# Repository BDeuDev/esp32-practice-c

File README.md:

# ESP32 Learning Journey

This repository documents my hands-on journey into Embedded Systems and Firmware Engineering using the ESP32 and ESP-IDF with The C Programming Language.

The goal is to learn by building. Each project focuses on a specific concept, peripheral, or embedded programming technique while improving my understanding of electronics, real-time systems, hardware debugging, and firmware development.

Rather than creating production-ready applications, this repository serves as a collection of experiments, exercises, and practical projects that help me develop embedded engineering skills.

## What I'm Learning

* GPIO and Digital Electronics
* FreeRTOS
* Timers and Scheduling
* Interrupts
* UART, SPI, and I2C
* PWM, ADC, and DAC
* Sensors and Actuators
* Wi-Fi and Bluetooth
* Hardware Debugging
* PCB Design with KiCad
* ESP-IDF Development

## Repository Structure

```mermaid
graph TD
    ROOT[ESP32 Learning Journey]

    ROOT --> BLINK[01_blink]
    ROOT --> TRAFFIC[02_traffic_light]
    ROOT --> BUTTON[03_button]
    ROOT --> PWM[04_pwm_led]
    ROOT --> ADC[05_adc_potentiometer]

    BLINK --> BLINK_README[README.md]
    BLINK --> BLINK_FW[firmware]
    BLINK --> BLINK_HW[hardware]

    TRAFFIC --> TRAFFIC_README[README.md]
    TRAFFIC --> TRAFFIC_FW[firmware]
    TRAFFIC --> TRAFFIC_HW[hardware]

    BUTTON --> BUTTON_README[README.md]
    BUTTON --> BUTTON_FW[firmware]
    BUTTON --> BUTTON_HW[hardware]

    PWM --> PWM_README[README.md]
    PWM --> PWM_FW[firmware]
    PWM --> PWM_HW[hardware]

    ADC --> ADC_README[README.md]
    ADC --> ADC_FW[firmware]
    ADC --> ADC_HW[hardware]
```

## Projects

| Project                                                   | Concept                                         |
| --------------------------------------------------------- | ----------------------------------------------- |
| [01 - Blink](./01_blink/README.md)                        | Basic GPIO output and ESP-IDF project structure |
| [02 - Traffic Light](./02_traffic_light/README.md)        | Multiple GPIO outputs and timing control        |
| [03 - Button](./03_button/README.md)                      | GPIO input, ISR and IRAM attr                   |
| [04 - PWM LED](./04_pwm_led/README.md)                    | PWM (Pulse Width Modulation)                    |
| [05 - ADC Potentiometer](./05_adc_potentiometer/README.md)| ADC (Analog-to-Digital Conversion)              |

## Why This Repository Exists

I created this repository to:

* Track my progress in embedded development.
* Document what I learn while working with ESP32 devices.
* Practice firmware engineering concepts through real projects.
* Build a portfolio that reflects my growth as an embedded developer.
* Create a reference for future projects.

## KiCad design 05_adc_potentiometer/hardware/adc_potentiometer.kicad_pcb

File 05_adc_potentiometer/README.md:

# 05 - ADC Potentiometer

A simple ESP32 project used to learn ADC (Analog-to-Digital Conversion) and how to work with a 7x4 segment display.

## Demo

## PCB Design

### Schematic

### PCB Top Layer

### PCB Bottom Layer

## 3D Model

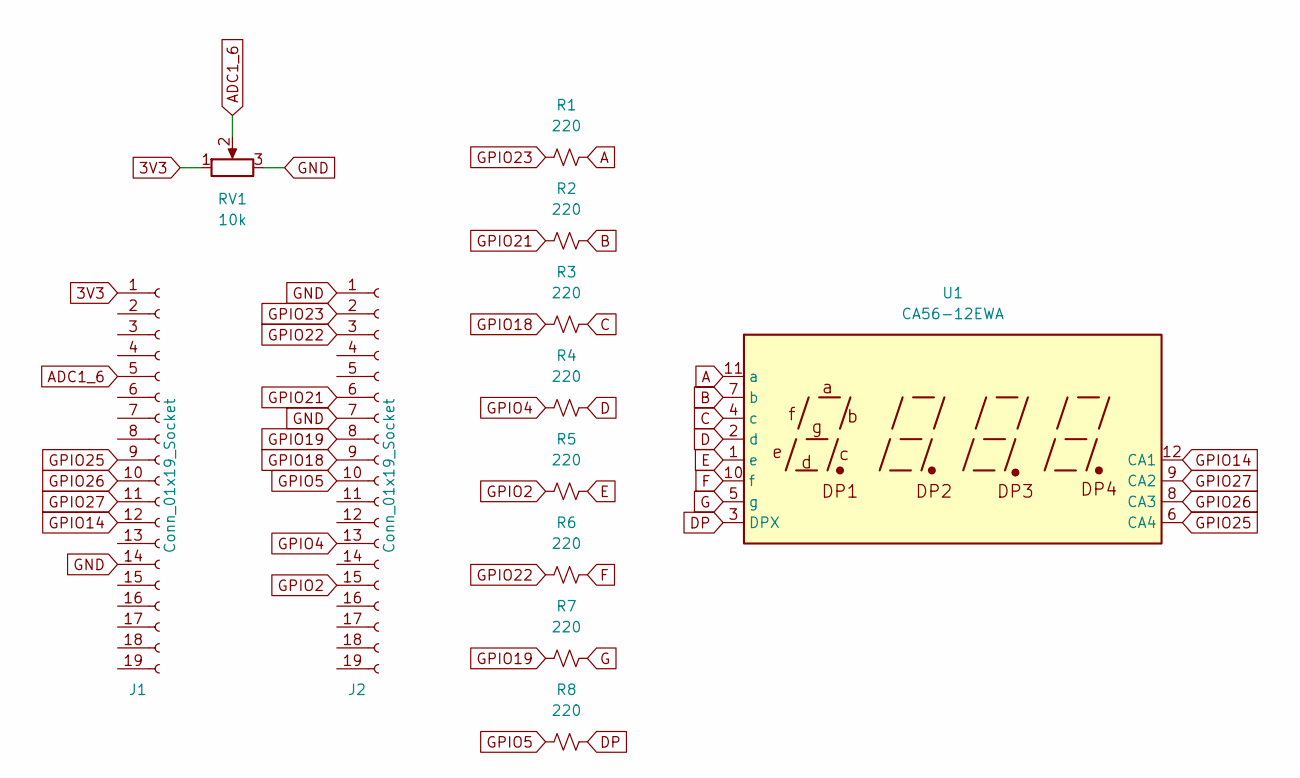
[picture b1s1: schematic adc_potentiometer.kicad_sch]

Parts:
J1, J2: Conn_01x19_Socket; PinSocket_1x19_P2.54mm_Vertical
R1, R2, R3, R4, R5, R6, R7, R8: 220; R_Axial_DIN0207_L6.3mm_D2.5mm_P15.24mm_Horizontal
RV1: 10k; Potentiometer_Bourns_3314G_Vertical
U1: CA56-12EWA; CA56-12SEKWA

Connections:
3V3: J1.1, RV1.1
A: R1.2, U1.11 (a)
ADC1_6: J1.5, RV1.2
B: R2.2, U1.7 (b)
C: R3.2, U1.4 (c)
D: R4.2, U1.2 (d)
DP: R8.2, U1.3 (DPX)
E: R5.2, U1.1 (e)
F: R6.2, U1.10 (f)
G: R7.2, U1.5 (g)
GND: J1.14, J2.1, J2.7, RV1.3
GPIO2: J2.15, R5.1
GPIO4: J2.13, R4.1
GPIO5: J2.10, R8.1
GPIO14: J1.12, U1.12 (CA1)
GPIO18: J2.9, R3.1
GPIO19: J2.8, R7.1
GPIO21: J2.6, R2.1
GPIO22: J2.3, R6.1
GPIO23: J2.2, R1.1
GPIO25: J1.9, U1.6 (CA4)
GPIO26: J1.10, U1.8 (CA3)
GPIO27: J1.11, U1.9 (CA2)

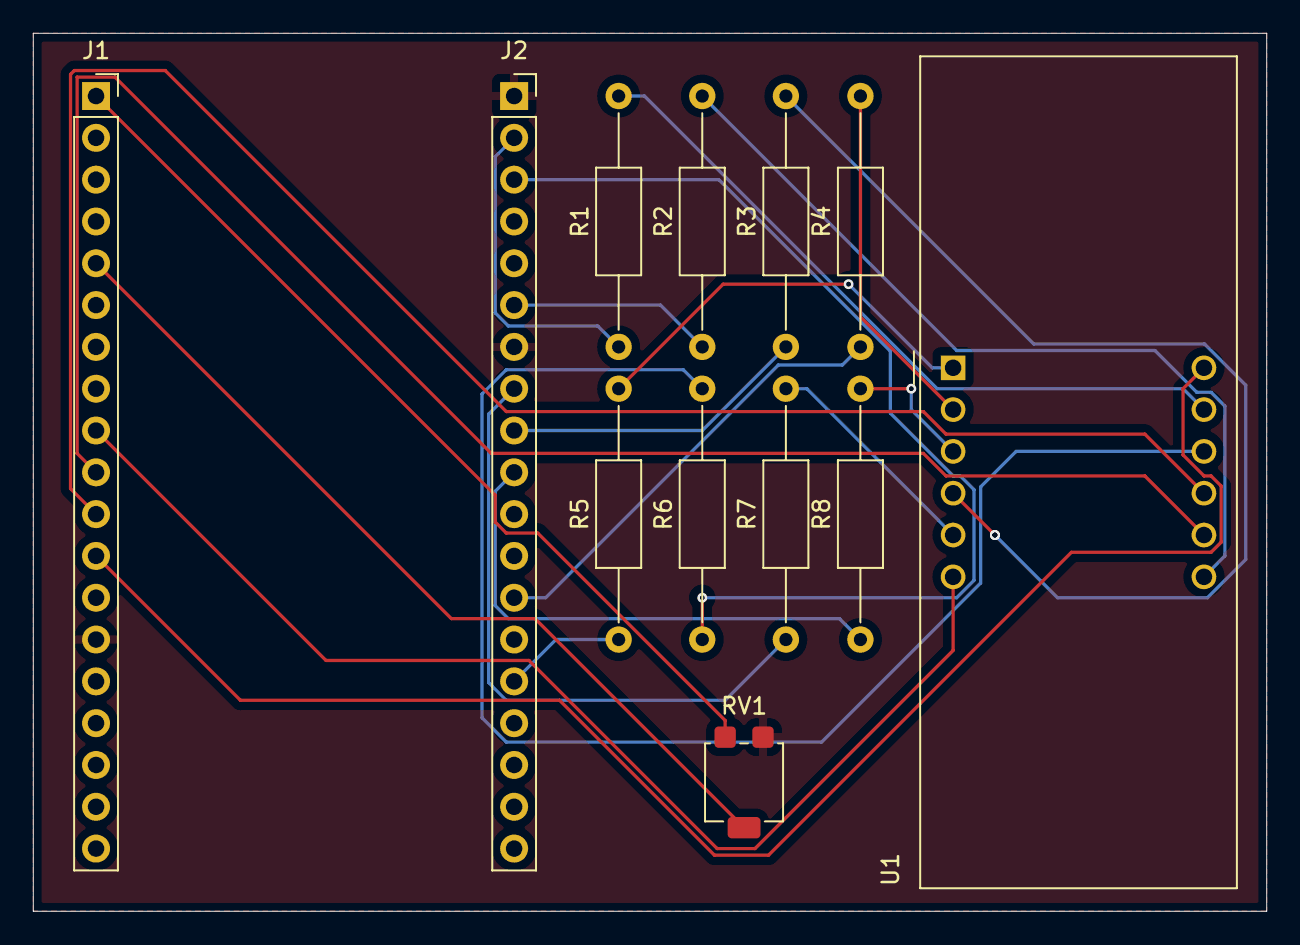
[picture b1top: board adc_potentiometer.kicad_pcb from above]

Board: 2 copper layers, 74.9 x 53.3 mm, 12 parts (0 on the bottom side), 23 nets.

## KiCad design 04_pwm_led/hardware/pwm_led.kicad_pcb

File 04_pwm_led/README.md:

# 04 - PWM LED

A simple ESP32 project used to learn PWM (Pulse Width Modulation) with duty cycles.

## Demo

## PCB Design

### Schematic

### PCB Top Layer

### PCB Bottom Layer

## 3D Model

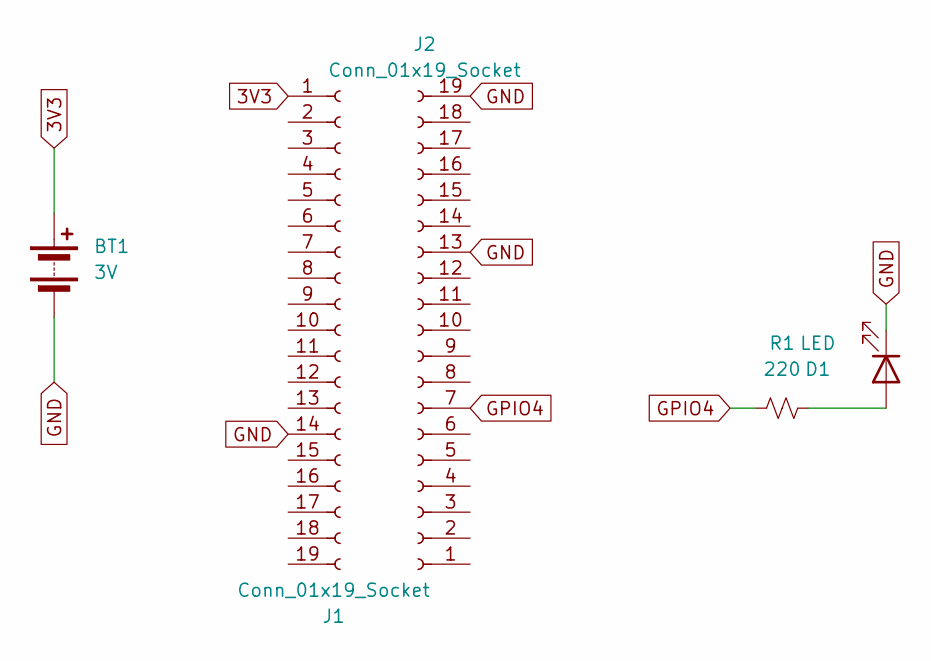
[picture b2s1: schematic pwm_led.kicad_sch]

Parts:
BT1: 3V; BatteryHolder_Keystone_2462_2xAA
D1: LED; LED_D3.0mm
J1, J2: Conn_01x19_Socket; PinSocket_1x19_P2.54mm_Vertical
R1: 220; R_Axial_DIN0204_L3.6mm_D1.6mm_P7.62mm_Horizontal

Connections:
3V3: BT1.1 (+), J1.1
GND: BT1.2 (-), D1.1 (K), J1.14, J2.13, J2.19
GPIO4: J2.7, R1.1
unnamed: D1.2 (A), R1.2

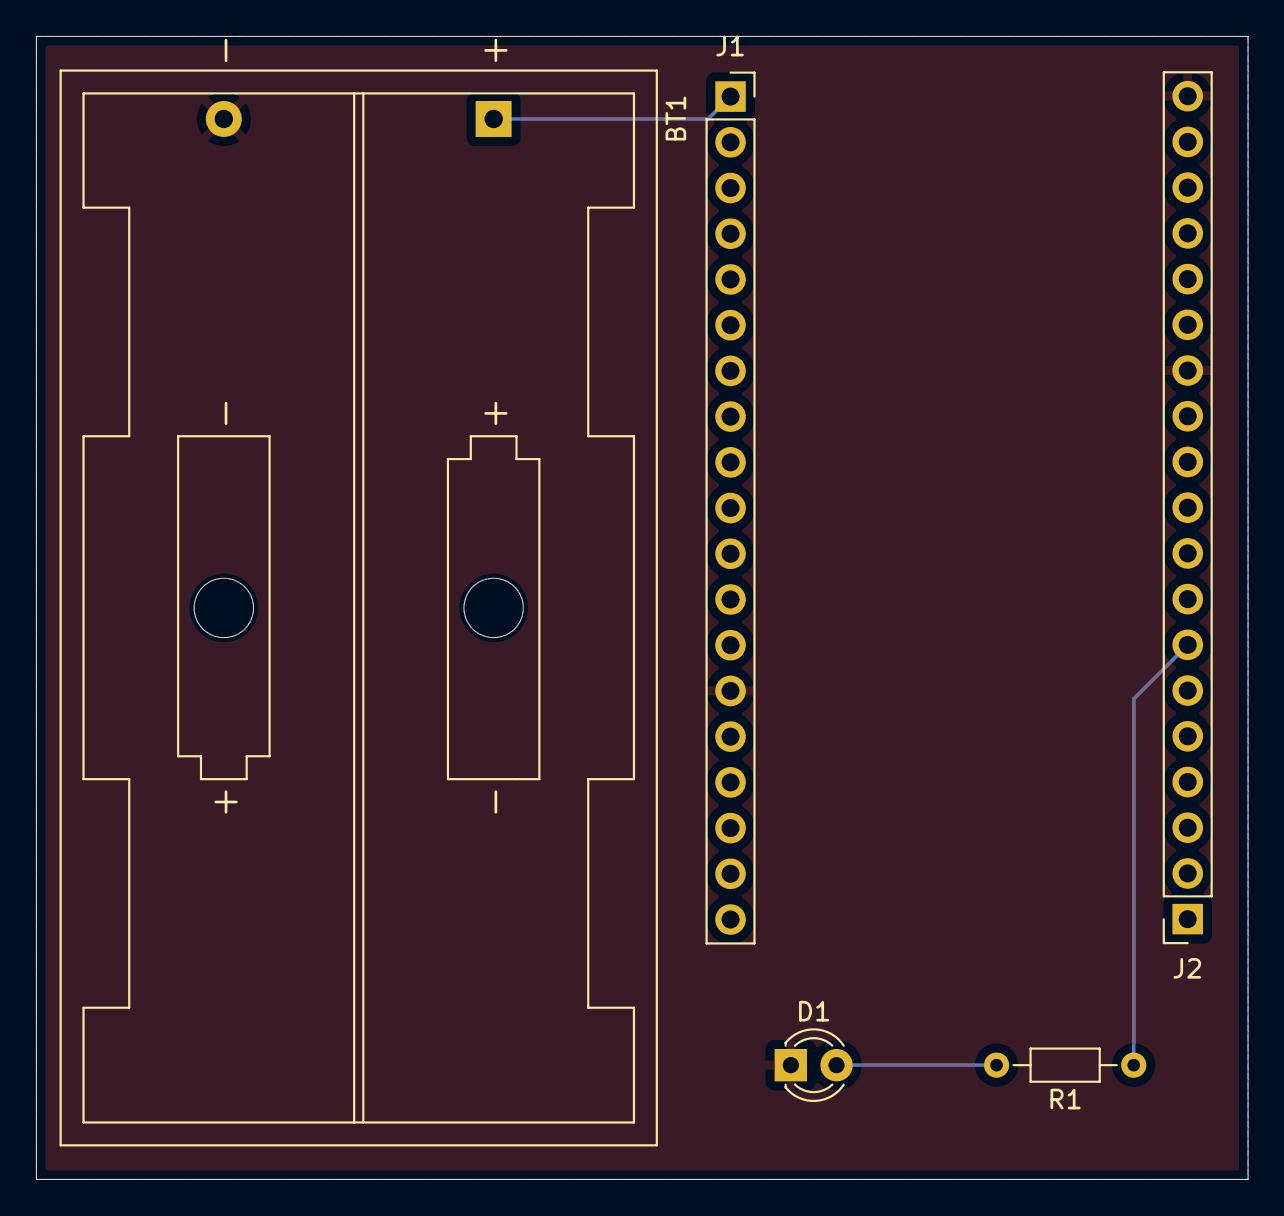
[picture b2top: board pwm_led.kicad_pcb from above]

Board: 2 copper layers, 67.3 x 63.5 mm, 5 parts (0 on the bottom side), 4 nets.

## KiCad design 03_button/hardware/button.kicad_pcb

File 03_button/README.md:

# 03 - Button

A simple ESP32 project used to learn GPIO input, events, ISR, queue, IRAM attr.

## Demo

## PCB Design

### Schematic

### PCB Top Layer

### PCB Bottom Layer

## 3D Model

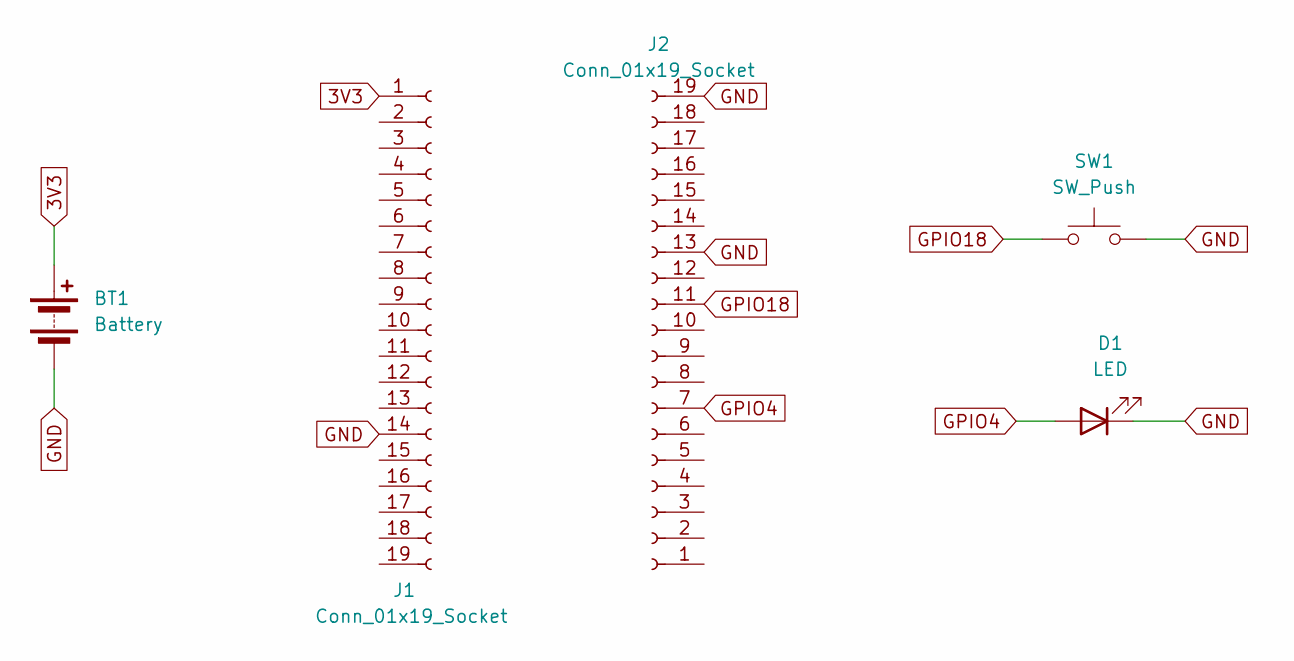
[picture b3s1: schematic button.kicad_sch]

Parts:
BT1: Battery; BatteryHolder_Keystone_2462_2xAA
D1: LED; LED_D3.0mm
J1, J2: Conn_01x19_Socket; PinSocket_1x19_P2.54mm_Vertical
SW1: SW_Push; SW_PUSH_6mm

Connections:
3V3: BT1.1 (+), J1.1
GND: BT1.2 (-), D1.1 (K), J1.14, J2.13, J2.19, SW1.2
GPIO4: D1.2 (A), J2.7
GPIO18: J2.11, SW1.1

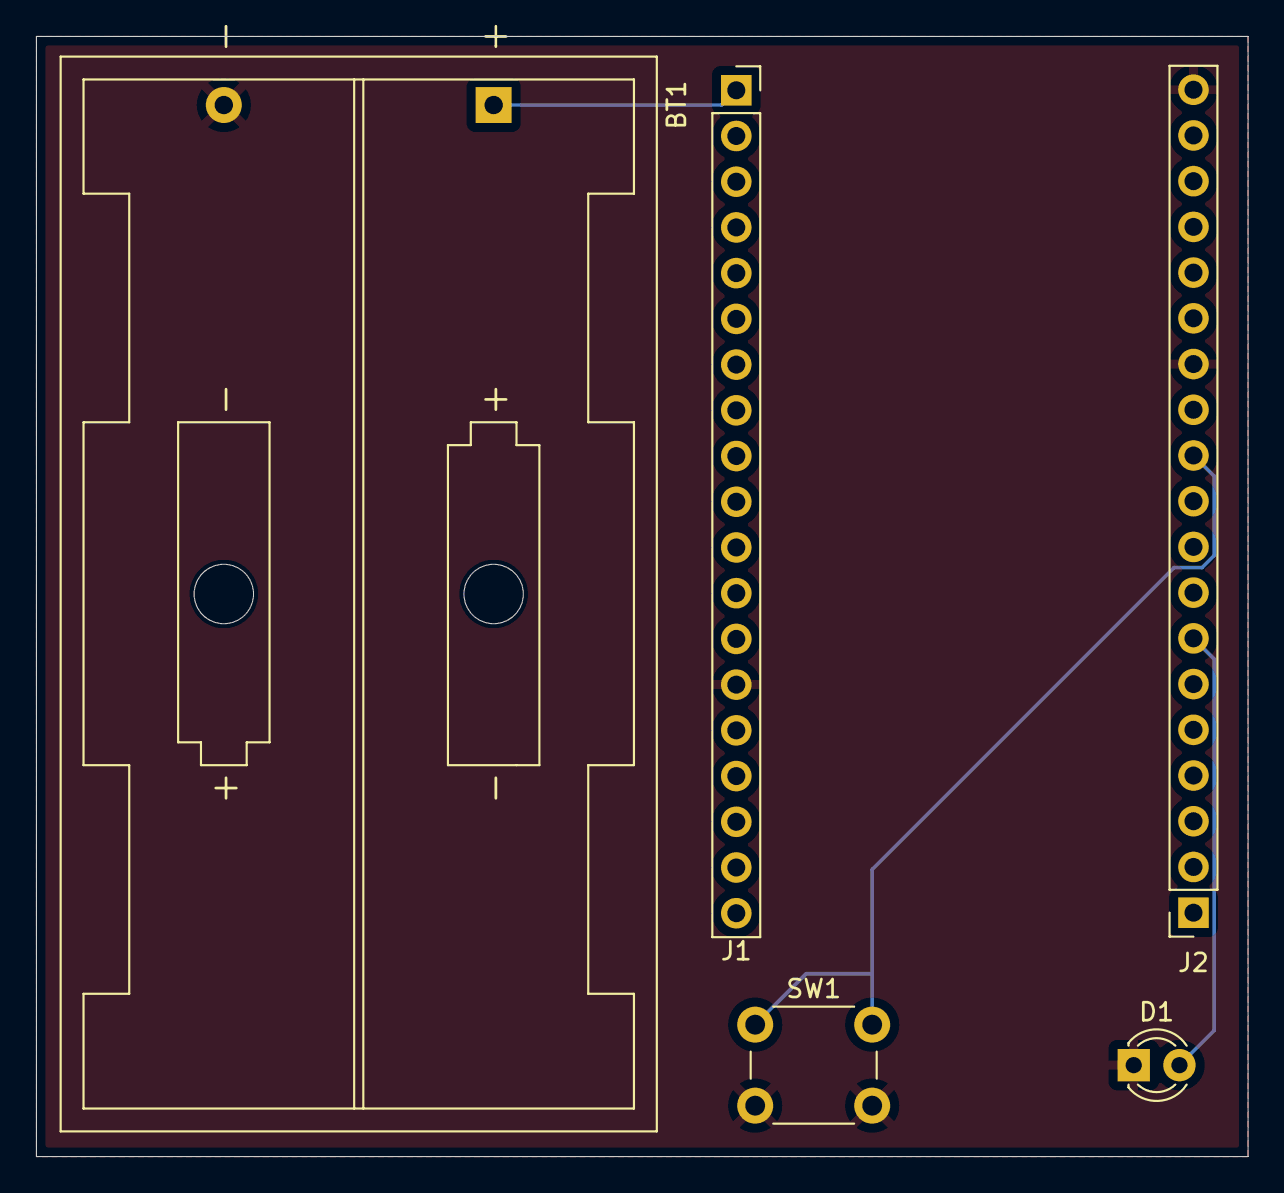
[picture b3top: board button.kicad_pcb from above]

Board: 2 copper layers, 67.3 x 62.2 mm, 5 parts (0 on the bottom side), 4 nets.

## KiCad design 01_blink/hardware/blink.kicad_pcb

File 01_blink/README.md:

# 01 - Blink

A simple ESP32 project used to learn GPIO output and the ESP-IDF workflow.

## Demo

## PCB Design

### Schematic

### PCB Top Layer

### PCB Bottom Layer

## 3D Model

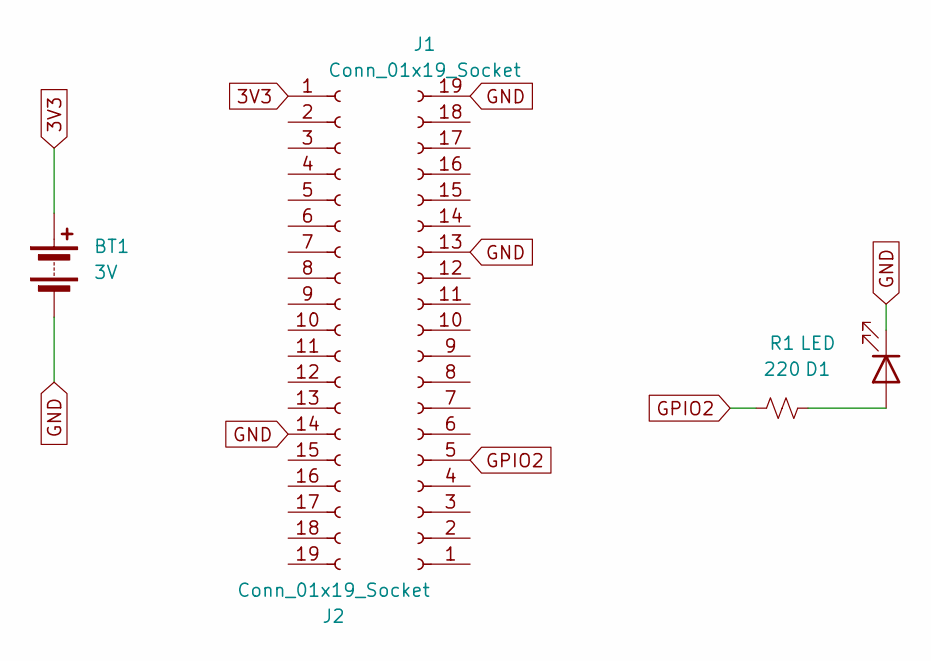
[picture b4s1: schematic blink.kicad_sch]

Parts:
BT1: 3V; BatteryHolder_Keystone_2462_2xAA
D1: LED; LED_D3.0mm
J1, J2: Conn_01x19_Socket; PinSocket_1x19_P2.54mm_Vertical
R1: 220; R_Axial_DIN0204_L3.6mm_D1.6mm_P7.62mm_Horizontal

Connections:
3V3: BT1.1 (+), J2.1
GND: BT1.2 (-), D1.1 (K), J1.13, J1.19, J2.14
GPIO2: J1.5, R1.1
unnamed: D1.2 (A), R1.2

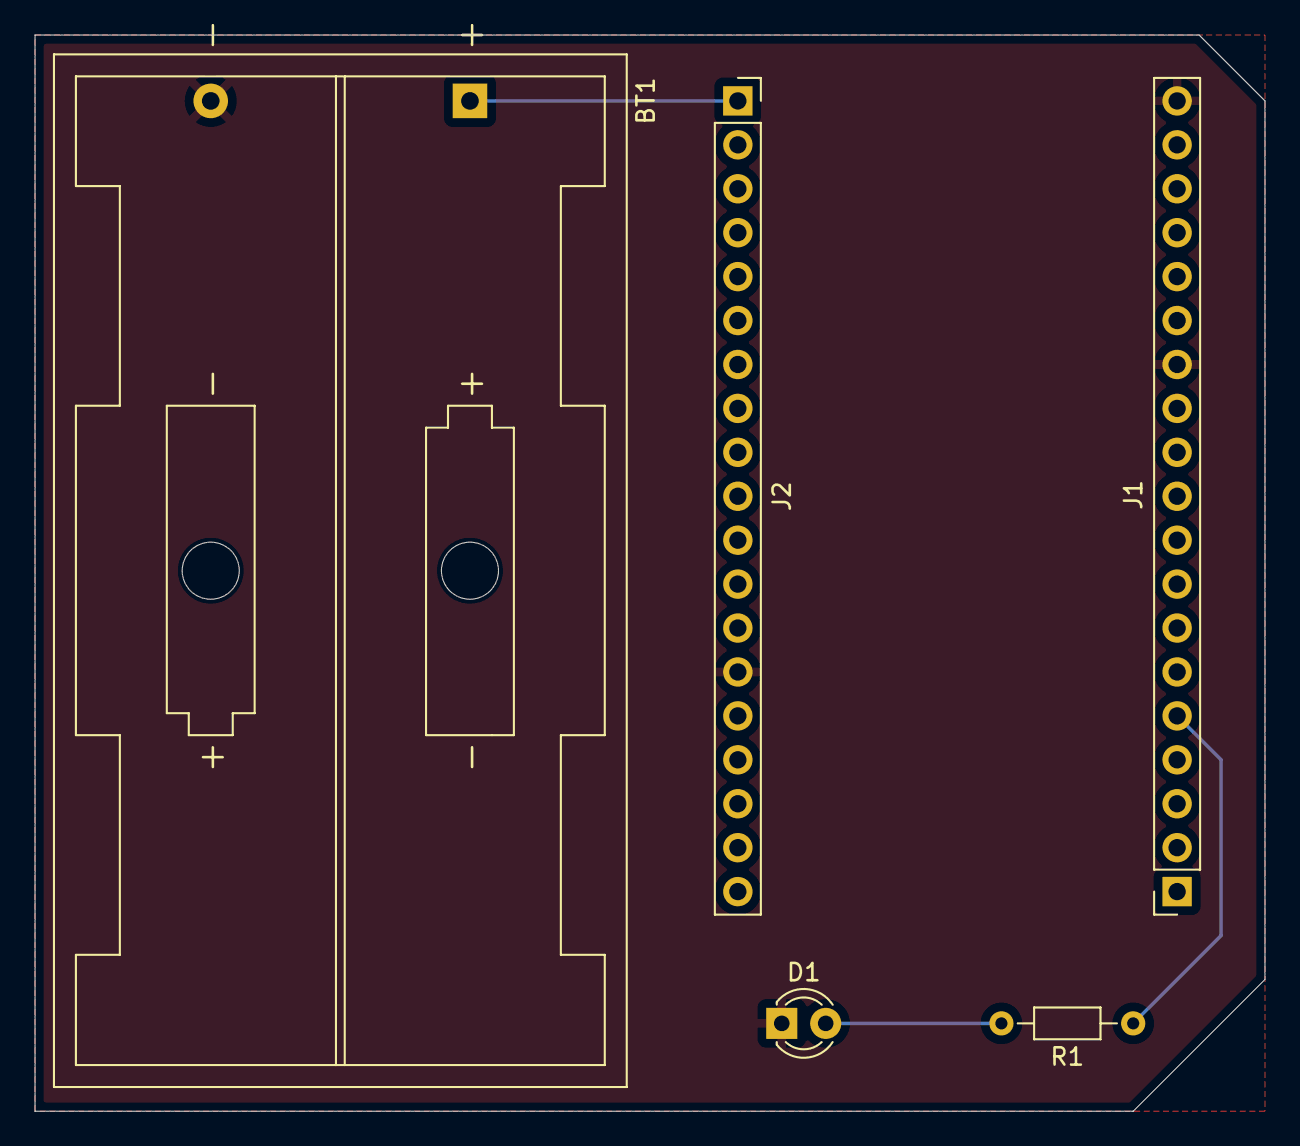
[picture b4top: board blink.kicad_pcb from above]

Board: 2 copper layers, 71.1 x 62.2 mm, 5 parts (0 on the bottom side), 4 nets.

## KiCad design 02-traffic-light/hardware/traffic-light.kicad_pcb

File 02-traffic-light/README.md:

# 02 - Traffic Light

A simple ESP32 project used to learn multiple GPIO output, Tasks and the ESP-IDF workflow.

## Demo

## PCB Design

### Schematic

### PCB Top Layer

### PCB Bottom Layer

## 3D Model

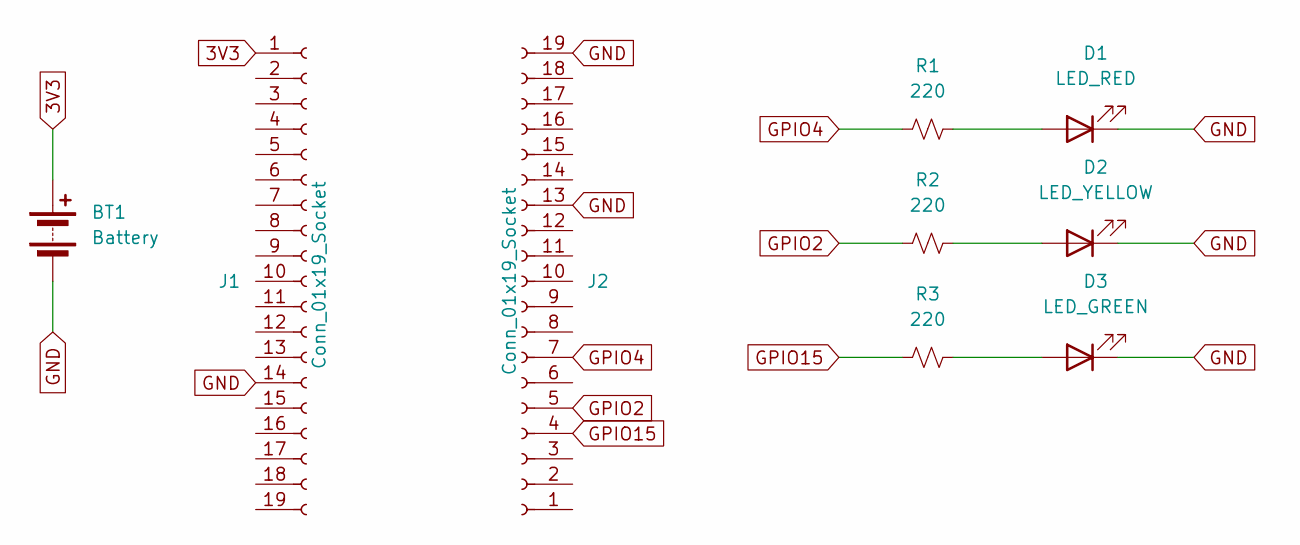
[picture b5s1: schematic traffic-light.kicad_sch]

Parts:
BT1: Battery; BatteryHolder_Keystone_2462_2xAA
D1: LED_RED; LED_D3.0mm
D2: LED_YELLOW; LED_D3.0mm
D3: LED_GREEN; LED_D3.0mm
J1, J2: Conn_01x19_Socket; PinSocket_1x19_P2.54mm_Vertical
R1, R2, R3: 220; R_Axial_DIN0204_L3.6mm_D1.6mm_P7.62mm_Horizontal

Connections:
3V3: BT1.1 (+), J1.1
GND: BT1.2 (-), D1.1 (K), D2.1 (K), D3.1 (K), J1.14, J2.13, J2.19
GPIO2: J2.5, R2.1
GPIO4: J2.7, R1.1
GPIO15: J2.4, R3.1
unnamed: D1.2 (A), R1.2
unnamed: D2.2 (A), R2.2
unnamed: D3.2 (A), R3.2

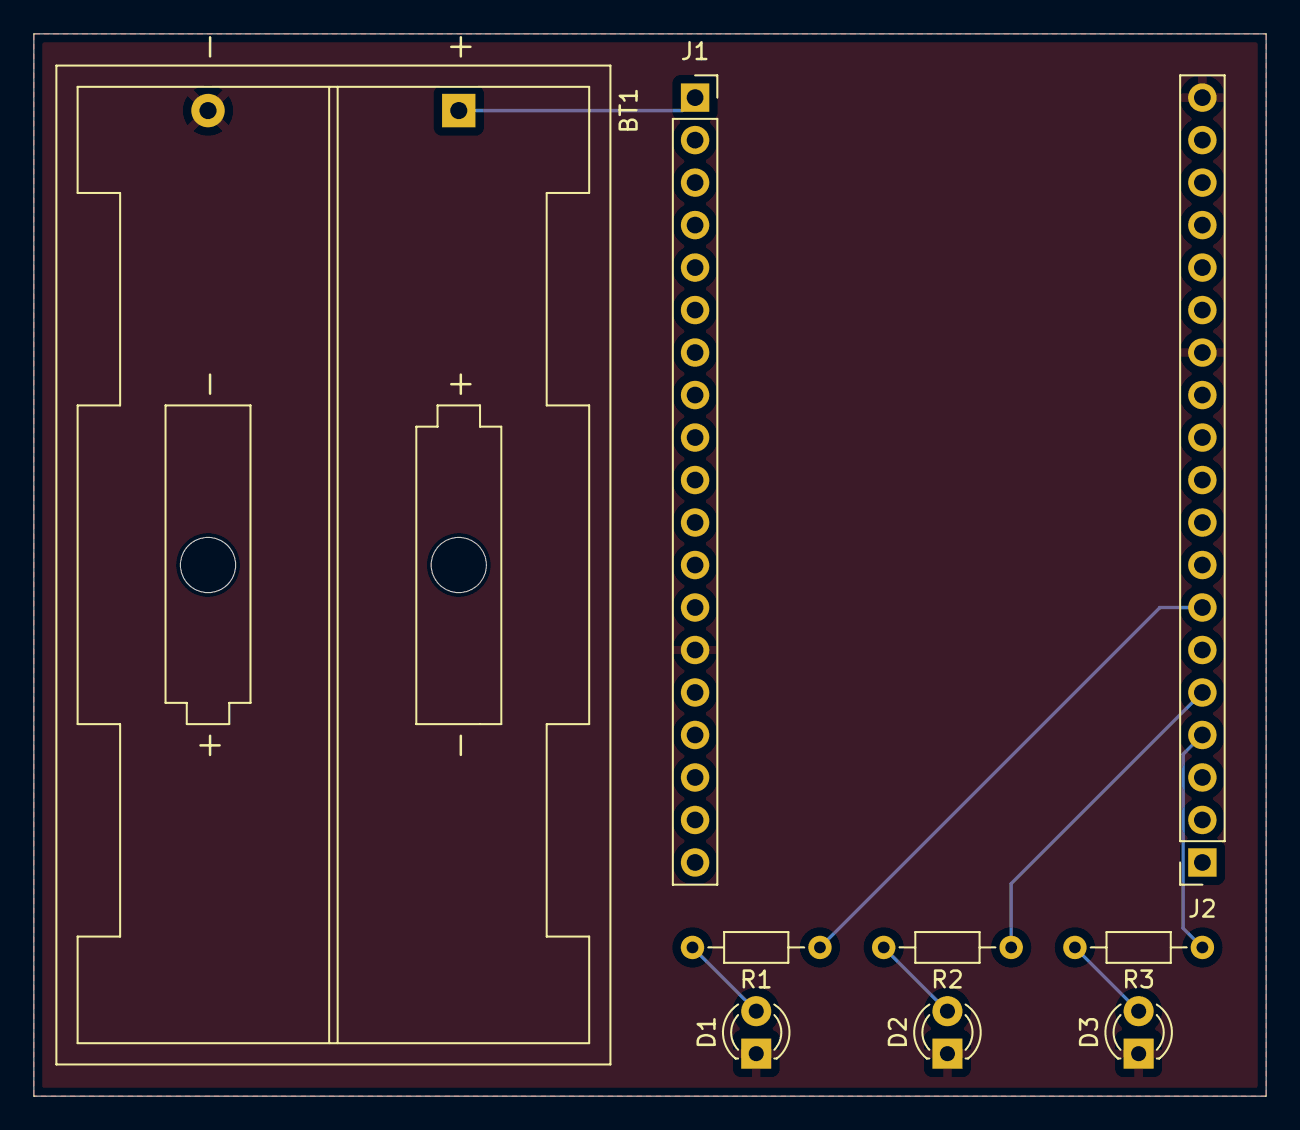
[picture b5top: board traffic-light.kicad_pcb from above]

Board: 2 copper layers, 73.7 x 63.5 mm, 9 parts (0 on the bottom side), 8 nets.

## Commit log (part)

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2026-06-20 Initial simple GPIO projects
2026-06-20 fix: rename traffic light dir
2026-06-23 03_button project
2026-06-26 04_pwm_led project
